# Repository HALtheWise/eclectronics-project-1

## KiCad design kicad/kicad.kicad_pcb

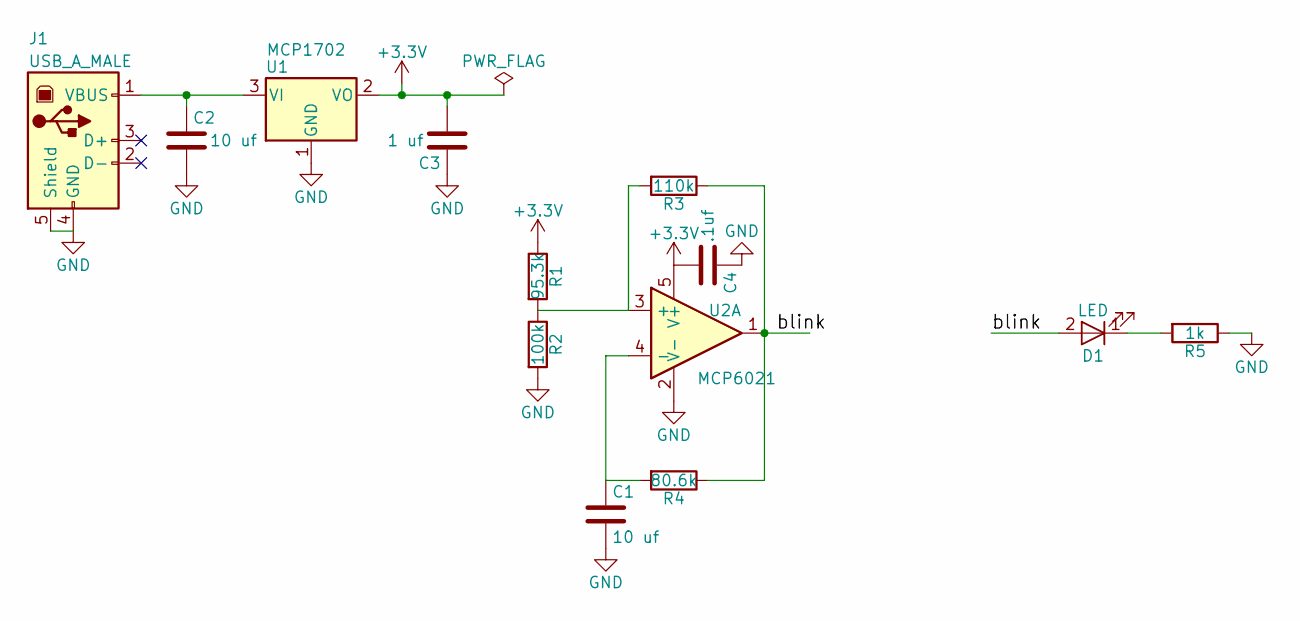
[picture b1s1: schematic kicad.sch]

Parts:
C1, C2: 10 uf; C_0805
C3: 1 uf; C_0603
C4: .1uf; C_0603
D1: LED; LED_0805
J1: USB_A_MALE; USB_A_male
R1: 95.3k; R_0603
R2: 100k; R_0603
R3: 110k; R_0603
R4: 80.6k; R_0603
R5: 1k; R_0603
U1: MCP1702; SOT-23
U2: MCP6021; SOT-23-5

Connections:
+3V3: C3.2, C4.2, R1.1, U1.2 (VO), U2.5 (V+)
/blink: D1.2 (A), R3.1, R4.1, U2.1
GND: C1.2, C2.2, C3.1, C4.1, J1.4 (GND), J1.5 (Shield), R2.2, R5.1, U1.1 (GND), U2.2 (V-)
unnamed: C1.1, R4.2, U2.4 (-)
unnamed: C2.1, J1.1 (VBUS), U1.3 (VI)
unnamed: D1.1 (K), R5.2
unnamed: R1.2, R2.1, R3.2, U2.3 (+)

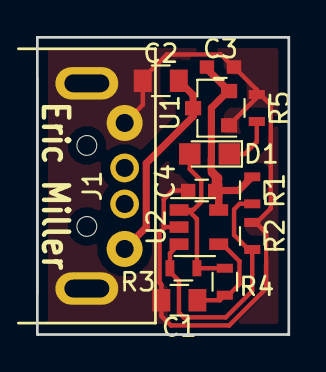
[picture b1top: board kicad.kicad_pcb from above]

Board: 2 copper layers, 14.0 x 16.5 mm, 13 parts (0 on the bottom side), 7 nets.

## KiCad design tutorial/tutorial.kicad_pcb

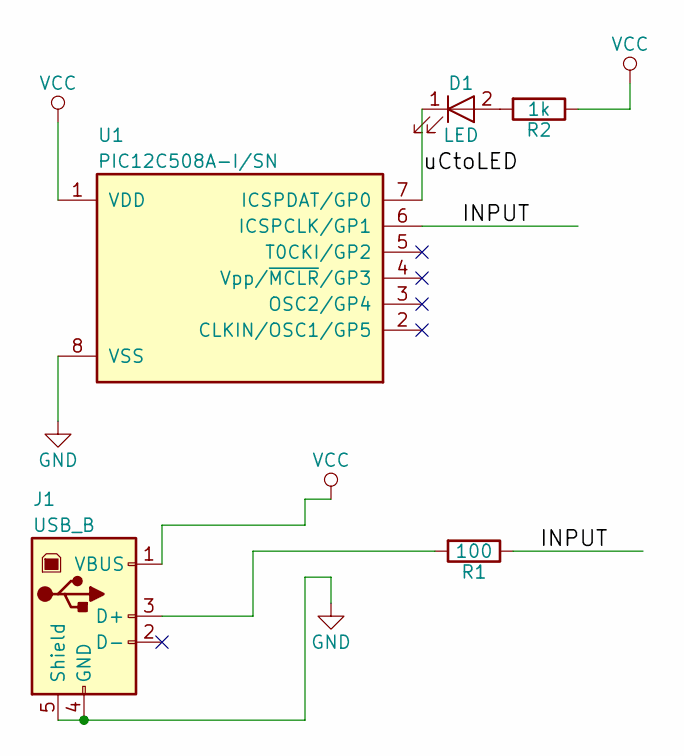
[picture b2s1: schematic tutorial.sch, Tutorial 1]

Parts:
D1: LED; LED_D5.0mm_Horizontal_O1.27mm_Z3.0mm
J1: USB_B; USB_Micro-B
R1: 100; R_0805_HandSoldering
R2: 1k; R_0805_HandSoldering
U1: PIC12C508A-I/SN; DIP-8_W7.62mm

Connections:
/INPUT: R1.1, U1.6 (ICSPCLK/GP1)
/uCtoLED: D1.1 (K), U1.7 (ICSPDAT/GP0)
GND: J1.4 (GND), J1.5 (Shield), U1.8 (VSS)
unnamed: D1.2 (A), R2.2
unnamed: J1.3 (D+), R1.2
VCC: J1.1 (VBUS), R2.1, U1.1 (VDD)

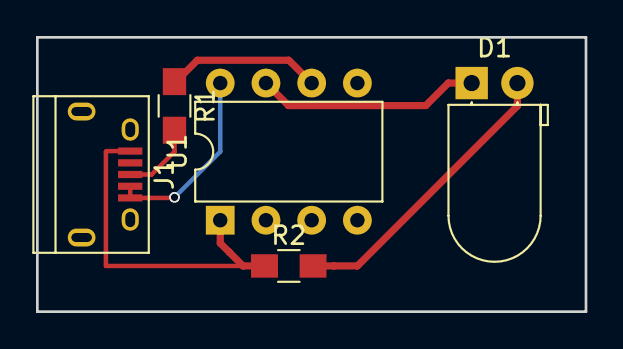
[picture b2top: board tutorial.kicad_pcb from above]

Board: 2 copper layers, 30.5 x 15.2 mm, 5 parts (0 on the bottom side), 6 nets.

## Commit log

2017-09-05 Completed tutorial using barrel jack connector
2017-09-05 Changed to microUSB connector
2017-09-05 Added project description PDF
2017-09-11 Began development of initial layout
2017-09-12 Added bypass caps
2017-09-12 Routed and stuff
2017-09-12 Added fill of ground plane on front
2017-09-13 Began explorations with LTspice
2017-09-13 Fixed resistor values in simulation
2017-09-13 Moved LTspice files to separate directory, created Mathematica analysis
2017-09-13 Removed old files
2017-09-13 Fixed capacitor size for large caps
2017-09-13 Finished board layout design for plug
2017-09-13 Layout stuff?
2017-09-13 Finished layout
2017-09-14 Exported sensitivity and schematic
